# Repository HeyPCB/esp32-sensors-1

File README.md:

# HeyPCB ESP32-S3 Sensors 1: Climate & Light

50 ESP32-S3 boards, one sensor each: temperature, humidity, pressure, CO2, gas, thermocouples and light. KiCad 10, JLCPCB-ready, CERN-OHL-S-2.0.

Every board is the same ESP32-S3 template with one sensor: ESP32-S3-WROOM-1-N16R8 (16 MB flash, 8 MB PSRAM, Wi-Fi + Bluetooth LE), USB-C with native USB and an ESD clamp, an AP2112K 3.3 V LDO, BOOT and RESET buttons, power and user LEDs; 30 x 48 mm, 4 layers.

| Wiring | ESP32-S3 pin |
|---|---|
| I2C SDA / SCL | IO8 / IO9 |
| Sensor interrupt | IO7 |
| Analog in | IO1 (ADC1 channel 0) |
| SPI SCK / MOSI / MISO / CS | IO12 / IO11 / IO13 / IO10 |
| Digital / 1-Wire / PDM | IO4, IO5, IO6 |
| User LED | IO48 |

## Boards (50)

| Board | Sensor | DRC errors / unconnected / parity |
|---|---|---|
| [S3 AM2302](boards/am2302/) | Aosong AM2302 (DHT22) humidity and temperature module | 0 / 0 / 0 |
| [S3 APDS-9306](boards/apds9306/) | Broadcom APDS-9306 ambient light sensor | 0 / 0 / 0 |
| [S3 BME280](boards/bme280/) | Bosch BME280 pressure, humidity and temperature sensor | 0 / 0 / 0 |
| [S3 BME680](boards/bme680/) | Bosch BME680 gas, pressure, humidity and temperature sensor | 0 / 0 / 0 |
| [S3 BME688](boards/bme688/) | Bosch BME688 gas, pressure, humidity and temperature sensor | 0 / 0 / 0 |
| [S3 DHT11](boards/dht11/) | Aosong DHT11 humidity and temperature module | 0 / 0 / 0 |
| [S3 DS18B20](boards/ds18b20/) | DS18B20 1-Wire temperature sensor (TO-92) | 0 / 0 / 0 |
| [S3 DS18B20](boards/ds18b20u/) | DS18B20 1-Wire temperature sensor (MSOP-8) | 0 / 0 / 0 |
| [S3 DS28EA00](boards/ds28ea00/) | Maxim DS28EA00 1-Wire temperature sensor with chain I/O | 0 / 0 / 0 |
| [S3 ENS210](boards/ens210/) | ScioSense ENS210 humidity and temperature sensor | 0 / 0 / 0 |
| [S3 GXHTC3](boards/gxhtc3/) | GXCAS GXHTC3 humidity and temperature sensor | 0 / 0 / 0 |
| [S3 HDC1080](boards/hdc1080/) | TI HDC1080 humidity and temperature sensor | 0 / 0 / 0 |
| [S3 HDC2080](boards/hdc2080/) | TI HDC2080 humidity and temperature sensor | 0 / 0 / 0 |
| [S3 KTY82](boards/kty82/) | NXP KTY82 silicon PTC temperature sensor | 0 / 0 / 0 |
| [S3 LDR](boards/ldr/) | GL5528 photoresistor light sensor | 0 / 0 / 0 |
| [S3 LM20](boards/lm20/) | TI LM20 analog temperature sensor | 0 / 0 / 0 |
| [S3 LM75B](boards/lm75b/) | NXP-style LM75B digital temperature sensor | 0 / 0 / 0 |
| [S3 LMT86](boards/lmt86/) | TI LMT86 analog temperature sensor | 0 / 0 / 0 |
| [S3 LMT87](boards/lmt87/) | LMT87 analog temperature sensor | 0 / 0 / 0 |
| [S3 LPS25HB](boards/lps25hb/) | ST LPS25HB MEMS pressure sensor | 0 / 0 / 0 |
| [S3 LTR-303](boards/ltr303/) | Lite-On LTR-303ALS ambient light sensor | 0 / 0 / 0 |
| [S3 MAX31855](boards/max31855/) | Maxim MAX31855K K-thermocouple converter | 0 / 0 / 0 |
| [S3 MAX31856](boards/max31856/) | Maxim MAX31856 universal thermocouple converter | 0 / 0 / 0 |
| [S3 MAX6675](boards/max6675/) | Maxim MAX6675 K-thermocouple converter | 0 / 0 / 0 |
| [S3 MCP9700](boards/mcp9700/) | Microchip MCP9700 analog temperature sensor | 0 / 0 / 0 |
| [S3 MCP9701A](boards/mcp9701/) | Microchip MCP9701A analog temperature sensor | 0 / 0 / 0 |
| [S3 MCP9808](boards/mcp9808/) | Microchip MCP9808 +-0.25 C digital temperature sensor | 0 / 0 / 0 |
| [S3 MPL3115A2](boards/mpl3115a2/) | NXP MPL3115A2 precision altimeter | 0 / 0 / 0 |
| [S3 MS5607](boards/ms5607/) | TE MS5607 barometric pressure sensor (10 cm altimeter) | 0 / 0 / 0 |
| [S3 MS5837](boards/ms5837/) | TE MS5837-30BA waterproof pressure / depth sensor | 0 / 0 / 0 |
| [S3 NTC](boards/ntc/) | Murata 10k NTC thermistor temperature sensor | 0 / 0 / 0 |
| [S3 SCD40](boards/scd40/) | Sensirion SCD40 photoacoustic CO2 sensor | 0 / 0 / 0 |
| [S3 SCD41](boards/scd41/) | Sensirion SCD41 photoacoustic CO2 sensor | 0 / 0 / 0 |
| [S3 SHT30](boards/sht30/) | Sensirion SHT30 humidity and temperature sensor | 0 / 0 / 0 |
| [S3 SHT31](boards/sht31/) | Sensirion SHT31 humidity and temperature sensor | 0 / 0 / 0 |
| [S3 SHT35](boards/sht35/) | Sensirion SHT35 high-accuracy humidity and temperature sensor | 0 / 0 / 0 |
| [S3 SHT40](boards/sht40/) | Sensirion SHT40 humidity and temperature sensor | 0 / 0 / 0 |
| [S3 SHT41](boards/sht41/) | Sensirion SHT41 humidity and temperature sensor | 0 / 0 / 0 |
| [S3 SHT45](boards/sht45/) | Sensirion SHT45 high-accuracy humidity and temperature sensor | 0 / 0 / 0 |
| [S3 SHTC3](boards/shtc3/) | Sensirion SHTC3 humidity and temperature sensor | 0 / 0 / 0 |
| [S3 TC1047A](boards/tc1047/) | Microchip TC1047A analog temperature sensor | 0 / 0 / 0 |
| [S3 TMP100](boards/tmp100/) | TI TMP100 digital temperature sensor | 0 / 0 / 0 |
| [S3 TMP101](boards/tmp101/) | TMP101 digital temperature sensor | 0 / 0 / 0 |
| [S3 TMP102](boards/tmp102/) | TI TMP102 digital temperature sensor | 0 / 0 / 0 |
| [S3 TMP1075](boards/tmp1075/) | TI TMP1075 digital temperature sensor | 0 / 0 / 0 |
| [S3 TMP112](boards/tmp112/) | TI TMP112 high-accuracy temperature sensor | 0 / 0 / 0 |
| [S3 TMP116](boards/tmp116/) | TI TMP116 0.2 C precision temperature sensor | 0 / 0 / 0 |
| [S3 TMP117](boards/tmp117/) | TI TMP117 0.1 C precision temperature sensor | 0 / 0 / 0 |
| [S3 TMP20](boards/tmp20/) | TI TMP20 analog temperature sensor | 0 / 0 / 0 |
| [S3 TMP235](boards/tmp235/) | TI TMP235 analog temperature sensor | 0 / 0 / 0 |

**Not fabricated, assembled or powered.** Every number in a board's README is measured by KiCad 10 on the files in its folder (`report.json`); parts carry LCSC numbers and were in JLCPCB's stock on the date each README gives.

Each board folder holds `kicad/` (project), `fab/` (Gerbers zip, BOM, CPL, STEP, schematic PDF), `media/` (renders) and `board.json` (the brief it was generated from).

Designed with the HeyPCB method on KiCad 10 by heypcb-kicad's headless pipeline with Freerouting 2.4.1.

## Licence

CERN-OHL-S-2.0, © 2026 heypcb.ai. See [LICENSE](LICENSE).

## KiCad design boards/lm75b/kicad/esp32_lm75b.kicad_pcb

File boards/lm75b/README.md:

# S3 LM75B

An ESP32-S3 board with NXP-style LM75B digital temperature sensor: USB-C, Wi-Fi and Bluetooth LE, ready to flash.

| Layers | Size | Parts | Nets | Connections routed | Vias | ERC errors | DRC errors / unconnected / parity |
|---|---|---|---|---|---|---|---|
| 4 | 30 x 48 mm | 24 | 15 | 71 -> 0 open | 33 | 0 | 0 / 0 / 0 |

**Not fabricated, assembled or powered.** Every number on this page is measured by KiCad 10 on the files in this folder; the full measurements are in [`report.json`](report.json).

| | |
|---|---|
| KiCad project | [`kicad/`](kicad/) |
| Gerbers, BOM, CPL, STEP, schematic PDF | [`fab/`](fab/) |
| Renders | [top](media/top.png), [bottom](media/bottom.png) |

A small ESP32-S3 development board built around one sensor: NXP-style LM75B digital temperature sensor. Plug in USB-C, flash it from Arduino, ESP-IDF or MicroPython over the ESP32-S3's native USB, and read the sensor. One of the HeyPCB ESP32 sensor series: the same ESP32-S3 template with a different sensor on each board. Designed with the HeyPCB method on KiCad 10, by heypcb-kicad's headless pipeline with Freerouting 2.4.1, from the brief in `board.json`.

## Specs

- **MCU:** ESP32-S3-WROOM-1-N16R8 (16 MB flash, 8 MB PSRAM, Wi-Fi + BLE 5), antenna over the top edge with no copper under it.
- **USB:** USB-C, native USB on the ESP32-S3 (no bridge chip), USBLC6-2 ESD clamp; BOOT (IO0) and RESET buttons.
- **Power:** USB 5 V to an AP2112K 3.3 V / 600 mA LDO; green power LED, blue user LED on IO48.
- **Sensor:** NXP-style LM75B digital temperature sensor. Wired to the ESP32-S3: I2C_SCL on IO9, I2C_SDA on IO8, SNS_INT on IO7.
- **Board:** 30 x 48 mm, 4 layers (In1 GND plane), 1.6 mm.
- **Sensor notes:** LM75B: A0-A2 to GND = address 0x48; OS (overtemperature) open drain, 10k pull-up, to IO7; 100 nF on +Vs. The KiCad symbol carries no footprint: TSSOP-8 3 x 3 mm is the LM75BDP's package.

## Parts

Every line carries an LCSC part number. Stock is JLCPCB's assembly stock on 2026-10-18.

| Designators | Value | LCSC | MPN | JLCPCB tier | Stock |
|---|---|---|---|---|---|
| C1 | 10uF | C15850 | CL21A106KAYNNNE | Basic | 6,481,857 |
| C2,C3,C6 | 1uF | C15849 | CL10A105KB8NNNC | Basic | 9,242,432 |
| C4 | 100nF | C14663 | CC0603KRX7R9BB104 | Basic | 32,334,212 |
| C5 | 22uF | C45783 | CL21A226MAQNNNE | Basic | 3,755,608 |
| C7 | 100nF | C1525 | CL05B104KO5NNNC | Basic | 29,476,420 |
| D1 | Blue (IO48) | C84266 | NCD0603B1 | Extended | 226,365 |
| D2 | Green (PWR) | C12624 | KT-0603G | Extended | 499,725 |
| J1 | USB-C | C165948 | TYPE-C-31-M-12 | Extended | 357,307 |
| R1,R2 | 5.1k | C25905 | 0402WGF5101TCE | Basic | 5,086,543 |
| R3,R6 | 10k | C25804 | 0603WAF1002T5E | Basic | 39,931,112 |
| R4 | 1k | C21190 | 0603WAF1001T5E | Basic | 23,204,357 |
| R5 | 2.2k | C4190 | 0603WAF2201T5E | Basic | 6,534,948 |
| R7,R8 | 4.7k | C23162 | 0603WAF4701T5E | Basic | 18,613,172 |
| SW1 | BOOT | C318884 | TS-1187A-B-A-B | Basic | 290,976 |
| SW2 | RESET | C318884 | TS-1187A-B-A-B | Basic | 290,976 |
| U1 | USBLC6-2SC6 | C7519 | USBLC6-2SC6 | Extended | 33,518 |
| U2 | AP2112K-3.3 | C51118 | AP2112K-3.3TRG1 | Extended | 6,345 |
| U3 | ESP32-S3-WROOM-1-N16R8 | C2913202 | ESP32-S3-WROOM-1-N16R8 | Extended | 32,329 |
| U4 | LM75BDP-MS | C18547812 | LM75BDP-MS | Extended | 2,484 |

## Ordering

- PCB: upload `fab/esp32_lm75b_gerbers.zip`, 4 layers, 30 x 48 mm, 1.6 mm.
- Assembly: `fab/esp32_lm75b_bom.csv` and `fab/esp32_lm75b_cpl_jlc.csv`, top side.
- The CPL is fitted to each part's own JLCPCB footprint, pad by pad, and re-checked by laying each footprint where its row says: 22 of 24 rows fitted, worst pin-to-pad offset 0.20 mm.
- Not fitted (no JLCPCB footprint to fit to), rotation from KiCad's: SW1, SW2. Check these in JLCPCB's placement preview.

## Notes

- The two TS-1187A buttons are placed with KiCad's rotation: KiCad's footprint and JLCPCB's land share a frame (pads at x +-3.0, y +-1.85 mm), but the automatic fit cannot confirm it because KiCad numbers the pads 1, 1, 2, 2.
- The USB-C receptacle renders as a plain box: KiCad's footprint names a 3D model KiCad does not ship.
- Not built or measured.

## How it was made

Designed with the HeyPCB method on KiCad 10, by heypcb-kicad's headless pipeline with Freerouting 2.4.1, from the brief in [`board.json`](board.json).

## Licence

CERN-OHL-S-2.0, © 2026 heypcb.ai. See the collection's LICENSE.

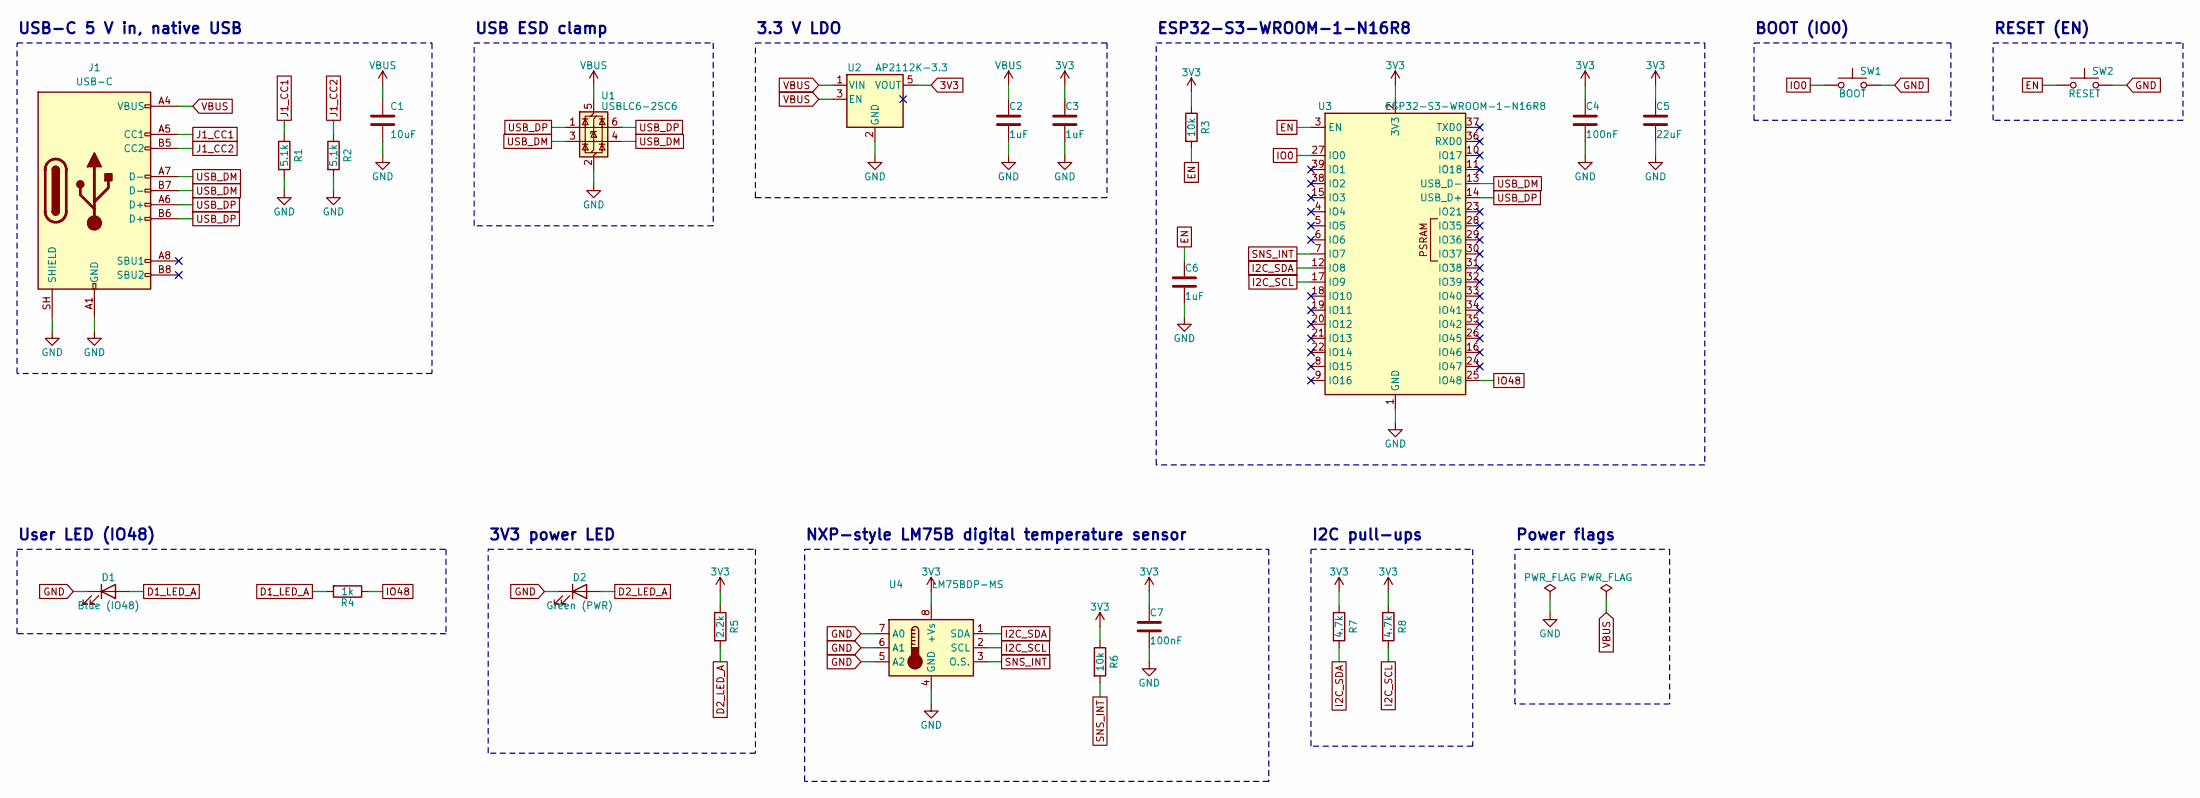
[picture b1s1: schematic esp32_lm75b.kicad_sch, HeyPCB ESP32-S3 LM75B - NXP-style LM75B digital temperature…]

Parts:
C1: 10uF; C_0805_2012Metric; MPN CL21A106KAYNNNE; LCSC C15850
C2, C3, C6: 1uF; C_0603_1608Metric; MPN CL10A105KB8NNNC; LCSC C15849
C4: 100nF; C_0603_1608Metric; MPN CC0603KRX7R9BB104; LCSC C14663
C5: 22uF; C_0805_2012Metric; MPN CL21A226MAQNNNE; LCSC C45783
C7: 100nF; C_0402_1005Metric; MPN CL05B104KO5NNNC; LCSC C1525
D1: Blue (IO48); LED_0603_1608Metric; MPN NCD0603B1; LCSC C84266
D2: Green (PWR); LED_0603_1608Metric; MPN KT-0603G; LCSC C12624
J1: USB-C; USB_C_Receptacle_HRO_TYPE-C-31-M-12; MPN TYPE-C-31-M-12; LCSC C165948
R1, R2: 5.1k; R_0402_1005Metric; MPN 0402WGF5101TCE; LCSC C25905
R3, R6: 10k; R_0603_1608Metric; MPN 0603WAF1002T5E; LCSC C25804
R4: 1k; R_0603_1608Metric; MPN 0603WAF1001T5E; LCSC C21190
R5: 2.2k; R_0603_1608Metric; MPN 0603WAF2201T5E; LCSC C4190
R7, R8: 4.7k; R_0603_1608Metric; MPN 0603WAF4701T5E; LCSC C23162
SW1: BOOT; SW_Push_1P1T_XKB_TS-1187A; MPN TS-1187A-B-A-B; LCSC C318884
SW2: RESET; SW_Push_1P1T_XKB_TS-1187A; MPN TS-1187A-B-A-B; LCSC C318884
U1: USBLC6-2SC6; SOT-23-6; MPN USBLC6-2SC6; LCSC C7519
U2: AP2112K-3.3; SOT-23-5; MPN AP2112K-3.3TRG1; LCSC C51118
U3: ESP32-S3-WROOM-1-N16R8; ESP32-S3-WROOM-1; MPN ESP32-S3-WROOM-1-N16R8; LCSC C2913202
U4: LM75BDP-MS; TSSOP-8_3x3mm_P0.65mm; MPN LM75BDP-MS; LCSC C18547812

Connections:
3V3: C3.1, C4.1, C5.1, C7.1, R3.1, R5.1, R6.1, R7.1, R8.1, U2.5 (VOUT), U3.2 (3V3), U4.8 (+Vs)
D1_LED_A: D1.2 (A), R4.2
D2_LED_A: D2.2 (A), R5.2
EN: C6.1, R3.2, SW2.1, U3.3 (EN)
GND: C1.2, C2.2, C3.2, C4.2, C5.2, C6.2, C7.2, D1.1 (K), D2.1 (K), J1.A1 (GND), J1.A12 (GND), J1.B1 (GND), J1.B12 (GND), J1.SH (SHIELD), R1.2, R2.2, SW1.2, SW2.2, U1.2 (GND), U2.2 (GND), U3.1 (GND), U3.40 (GND), U3.41 (GND), U4.4 (GND), U4.5 (A2), U4.6 (A1), U4.7 (A0)
I2C_SCL: R8.2, U3.17 (IO9), U4.2 (SCL)
I2C_SDA: R7.2, U3.12 (IO8), U4.1 (SDA)
IO0: SW1.1, U3.27 (IO0)
IO48: R4.1, U3.25 (IO48)
J1_CC1: J1.A5 (CC1), R1.1
J1_CC2: J1.B5 (CC2), R2.1
SNS_INT: R6.2, U3.7 (IO7), U4.3 (O.S.)
USB_DM: J1.A7 (D-), J1.B7 (D-), U1.3 (I/O2), U1.4 (I/O2), U3.13 (USB_D-)
USB_DP: J1.A6 (D+), J1.B6 (D+), U1.1 (I/O1), U1.6 (I/O1), U3.14 (USB_D+)
VBUS: C1.1, C2.1, J1.A4 (VBUS), J1.A9 (VBUS), J1.B4 (VBUS), J1.B9 (VBUS), U1.5 (VBUS), U2.1 (VIN), U2.3 (EN)

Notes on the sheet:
USB-C 5 V in, native USB
USB ESD clamp
3.3 V LDO
ESP32-S3-WROOM-1-N16R8
BOOT (IO0)
RESET (EN)
User LED (IO48)
3V3 power LED
NXP-style LM75B digital temperature sensor
I2C pull-ups
Power flags

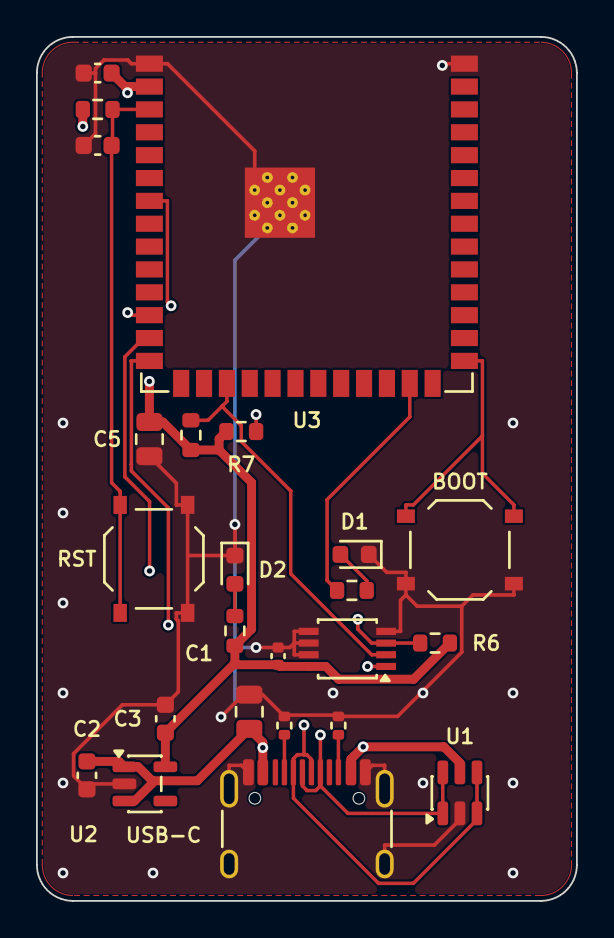
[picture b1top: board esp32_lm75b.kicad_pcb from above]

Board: 4 copper layers, 30.0 x 48.0 mm, 24 parts (0 on the bottom side), 15 nets.

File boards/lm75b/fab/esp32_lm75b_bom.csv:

"Reference","Value","Footprint","MPN","LCSC","Qty"
"C1","10uF","Capacitor_SMD:C_0805_2012Metric","CL21A106KAYNNNE","C15850","1"
"C2,C3,C6","1uF","Capacitor_SMD:C_0603_1608Metric","CL10A105KB8NNNC","C15849","3"
"C4","100nF","Capacitor_SMD:C_0603_1608Metric","CC0603KRX7R9BB104","C14663","1"
"C5","22uF","Capacitor_SMD:C_0805_2012Metric","CL21A226MAQNNNE","C45783","1"
"C7","100nF","Capacitor_SMD:C_0402_1005Metric","CL05B104KO5NNNC","C1525","1"
"D1","Blue (IO48)","LED_SMD:LED_0603_1608Metric","NCD0603B1","C84266","1"
"D2","Green (PWR)","LED_SMD:LED_0603_1608Metric","KT-0603G","C12624","1"
"J1","USB-C","Connector_USB:USB_C_Receptacle_HRO_TYPE-C-31-M-12","TYPE-C-31-M-12","C165948","1"
"R1,R2","5.1k","Resistor_SMD:R_0402_1005Metric","0402WGF5101TCE","C25905","2"
"R3,R6","10k","Resistor_SMD:R_0603_1608Metric","0603WAF1002T5E","C25804","2"
"R4","1k","Resistor_SMD:R_0603_1608Metric","0603WAF1001T5E","C21190","1"
"R5","2.2k","Resistor_SMD:R_0603_1608Metric","0603WAF2201T5E","C4190","1"
"R7,R8","4.7k","Resistor_SMD:R_0603_1608Metric","0603WAF4701T5E","C23162","2"
"SW1","BOOT","Button_Switch_SMD:SW_Push_1P1T_XKB_TS-1187A","TS-1187A-B-A-B","C318884","1"
"SW2","RESET","Button_Switch_SMD:SW_Push_1P1T_XKB_TS-1187A","TS-1187A-B-A-B","C318884","1"
"U1","USBLC6-2SC6","Package_TO_SOT_SMD:SOT-23-6","USBLC6-2SC6","C7519","1"
"U2","AP2112K-3.3","Package_TO_SOT_SMD:SOT-23-5","AP2112K-3.3TRG1","C51118","1"
"U3","ESP32-S3-WROOM-1-N16R8","RF_Module:ESP32-S3-WROOM-1","ESP32-S3-WROOM-1-N16R8","C2913202","1"
"U4","LM75BDP-MS","Package_SO:TSSOP-8_3x3mm_P0.65mm","LM75BDP-MS","C18547812","1"
